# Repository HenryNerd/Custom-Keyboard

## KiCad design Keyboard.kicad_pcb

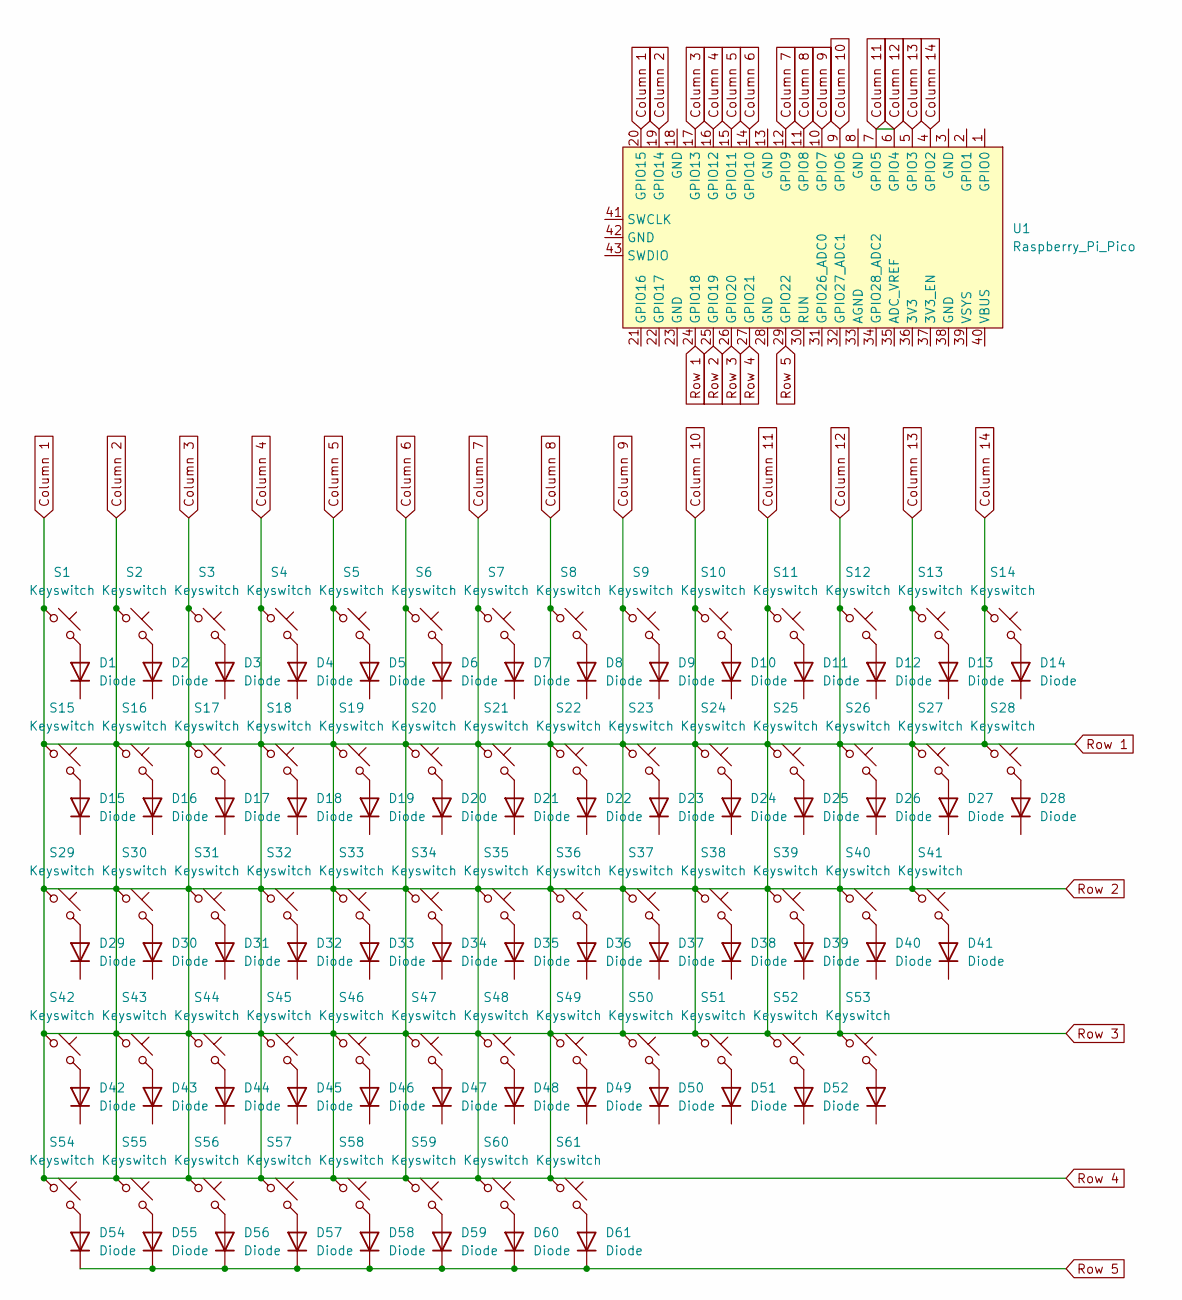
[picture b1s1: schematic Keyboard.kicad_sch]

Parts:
D1, D2, D3, D4, D5, D6, D7, D8, D9, D10, D11, D12, D13, D14, D15, D16, D17, D18, D19, D20, D21, D22, D23, D24, D25, D26, D27, D28, D29, D30, D31, D32, D33, D34, D35, D36, D37, D38, D39, D40, D41, D42, D43, D44, D45, D46, D47, D48, D49, D50, D51, D52, D53, D54, D55, D56, D57, D58, D59, D60, D61: Diode; Diode_DO-35
S1, S2, S3, S4, S5, S6, S7, S8, S9, S10, S11, S12, S13, S16, S17, S18, S19, S20, S21, S22, S23, S24, S25, S26, S27, S30, S31, S32, S33, S34, S35, S36, S37, S38, S39, S40, S43, S44, S45, S46, S47, S48, S49, S50, S51, S52, S59, S60, S61: Keyswitch; MX_PCB_1.00u
S14: Keyswitch; MX_PCB_2.00u
S15, S28: Keyswitch; MX_PCB_1.50u
S29: Keyswitch; MX_PCB_1.75u
S41: Keyswitch; MX_PCB_2.25u
S42, S53: Keyswitch; MX_PCB_2.50u
S54, S55, S56, S58: Keyswitch; MX_PCB_1.25u
S57: Keyswitch; MX_PCB_7.00u
U1: Raspberry_Pi_Pico

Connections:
Column 1: S1.1, S2.1, S3.1, S4.1, S5.1, S6.1, S7.1, S8.1, S9.1, S10.1, S11.1, S12.1, S13.1, S14.1, S15.1, S16.1, S17.1, S18.1, S19.1, S20.1, S21.1, S22.1, S23.1, S24.1, S25.1, S26.1, S27.1, S28.1, S29.1, S30.1, S31.1, S32.1, S33.1, S34.1, S35.1, S36.1, S37.1, S38.1, S39.1, S40.1, S41.1, S42.1, S43.1, S44.1, S45.1, S46.1, S47.1, S48.1, S49.1, S50.1, S51.1, S52.1, S53.1, S54.1, S55.1, S56.1, S57.1, S58.1, S59.1, S60.1, S61.1, U1.4 (GPIO2), U1.5 (GPIO3), U1.6 (GPIO4), U1.7 (GPIO5), U1.9 (GPIO6), U1.10 (GPIO7), U1.11 (GPIO8), U1.12 (GPIO9), U1.14 (GPIO10), U1.15 (GPIO11), U1.16 (GPIO12), U1.17 (GPIO13), U1.19 (GPIO14), U1.20 (GPIO15), U1.24 (GPIO18), U1.25 (GPIO19), U1.26 (GPIO20), U1.27 (GPIO21)
unnamed: D1.2 (A), S1.2
unnamed: D2.2 (A), S2.2
unnamed: D3.2 (A), S3.2
unnamed: D4.2 (A), S4.2
unnamed: D5.2 (A), S5.2
unnamed: D6.2 (A), S6.2
unnamed: D7.2 (A), S7.2
unnamed: D8.2 (A), S8.2
unnamed: D9.2 (A), S9.2
unnamed: D10.2 (A), S10.2
unnamed: D11.2 (A), S11.2
unnamed: D12.2 (A), S12.2
unnamed: D13.2 (A), S13.2
unnamed: D14.2 (A), S14.2
unnamed: D15.2 (A), S15.2
unnamed: D16.2 (A), S16.2
unnamed: D17.2 (A), S17.2
unnamed: D18.2 (A), S18.2
unnamed: D19.2 (A), S19.2
unnamed: D20.2 (A), S20.2
unnamed: D21.2 (A), S21.2
unnamed: D22.2 (A), S22.2
unnamed: D23.2 (A), S23.2
unnamed: D24.2 (A), S24.2
unnamed: D25.2 (A), S25.2
unnamed: D26.2 (A), S26.2
unnamed: D27.2 (A), S27.2
unnamed: D28.2 (A), S28.2
unnamed: D29.2 (A), S29.2
unnamed: D30.2 (A), S30.2
unnamed: D31.2 (A), S31.2
unnamed: D32.2 (A), S32.2
unnamed: D33.2 (A), S33.2
unnamed: D34.2 (A), S34.2
unnamed: D35.2 (A), S35.2
unnamed: D36.2 (A), S36.2
unnamed: D37.2 (A), S37.2
unnamed: D38.2 (A), S38.2
unnamed: D39.2 (A), S39.2
unnamed: D40.2 (A), S40.2
unnamed: D41.2 (A), S41.2
unnamed: D42.2 (A), S42.2
unnamed: D43.2 (A), S43.2
unnamed: D44.2 (A), S44.2
unnamed: D45.2 (A), S45.2
unnamed: D46.2 (A), S46.2
unnamed: D47.2 (A), S47.2
unnamed: D48.2 (A), S48.2
unnamed: D49.2 (A), S49.2
unnamed: D50.2 (A), S50.2
unnamed: D51.2 (A), S51.2
unnamed: D52.2 (A), S52.2
unnamed: D53.2 (A), S53.2
unnamed: D54.2 (A), S54.2
unnamed: D55.2 (A), S55.2
unnamed: D56.2 (A), S56.2
unnamed: D57.2 (A), S57.2
unnamed: D58.2 (A), S58.2
unnamed: D59.2 (A), S59.2
unnamed: D60.2 (A), S60.2
unnamed: D61.2 (A), S61.2
Row 5: D54.1 (K), D55.1 (K), D56.1 (K), D57.1 (K), D58.1 (K), D59.1 (K), D60.1 (K), D61.1 (K), U1.29 (GPIO22)

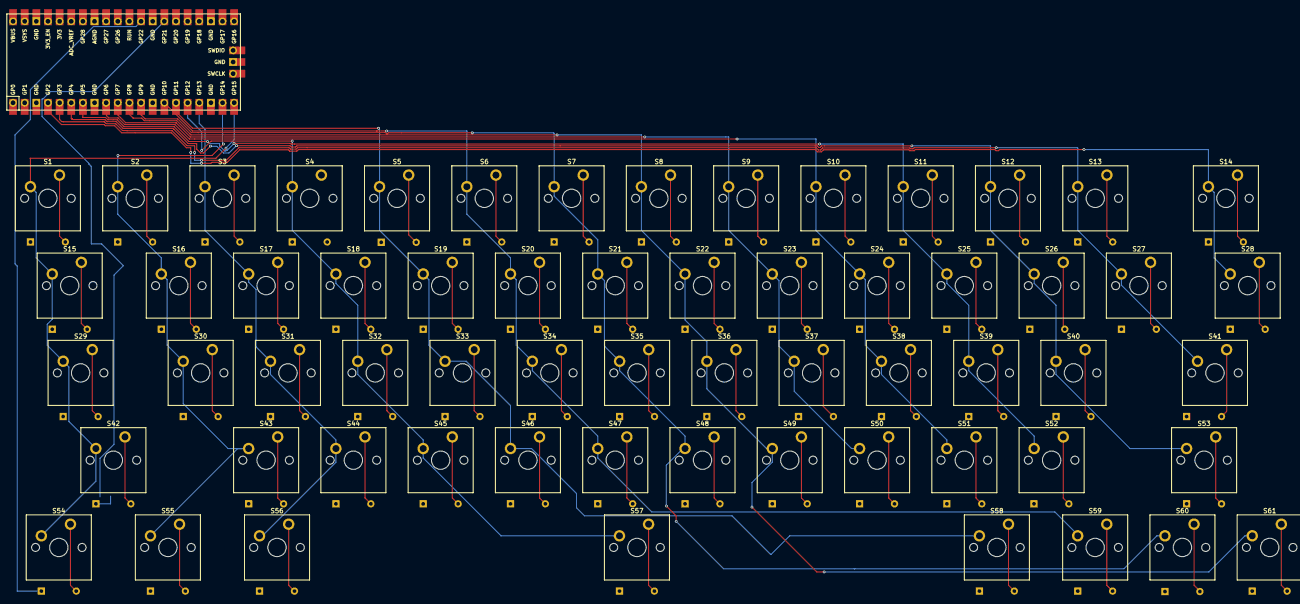
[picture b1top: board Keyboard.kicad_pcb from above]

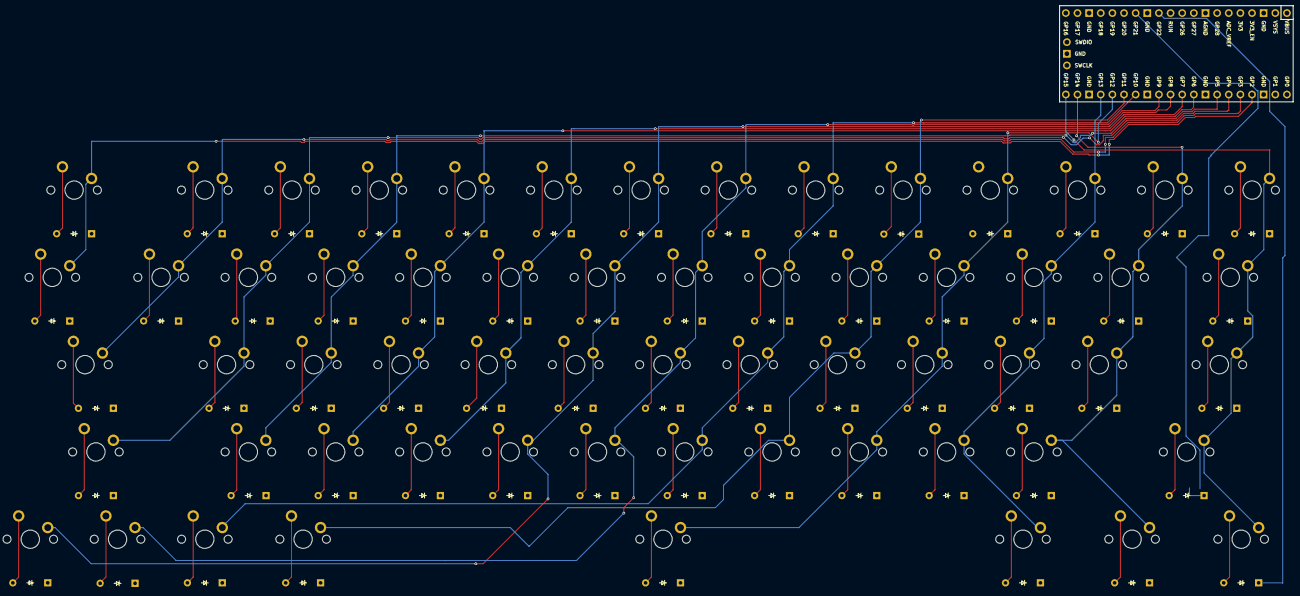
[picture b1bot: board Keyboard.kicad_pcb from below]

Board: 2 copper layers, 123 parts (61 on the bottom side), 63 nets.

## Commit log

2024-07-25 Added v1.0 KiCAD schematic
2024-07-26 Unfinished Start to PCB
2024-07-28 Update PCB with rougth layout
2024-07-29 start updating layout
2024-07-29 update layout and start wiring
2024-07-29 Continued working on wiring
2024-07-29 More wiring
